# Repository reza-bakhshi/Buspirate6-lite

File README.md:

# ⚠️ THIS PROJECT IS UNDER ACTIVE DEVELOPMENT AND TESTING  

## DO NOT MANUFACTURE OR USE THE HARDWARE WITHOUT YOUR OWN VERIFICATION

## Overview

This project is currently in progress. Features, hardware design, and functionality may change at any time. Use at your own risk.

---

## Images

### TOP

### BOTTOM

---

## Notes

- This project is not stable yet.
- Hardware and firmware are still being tested.
- Double-check everything before using or manufacturing.

---

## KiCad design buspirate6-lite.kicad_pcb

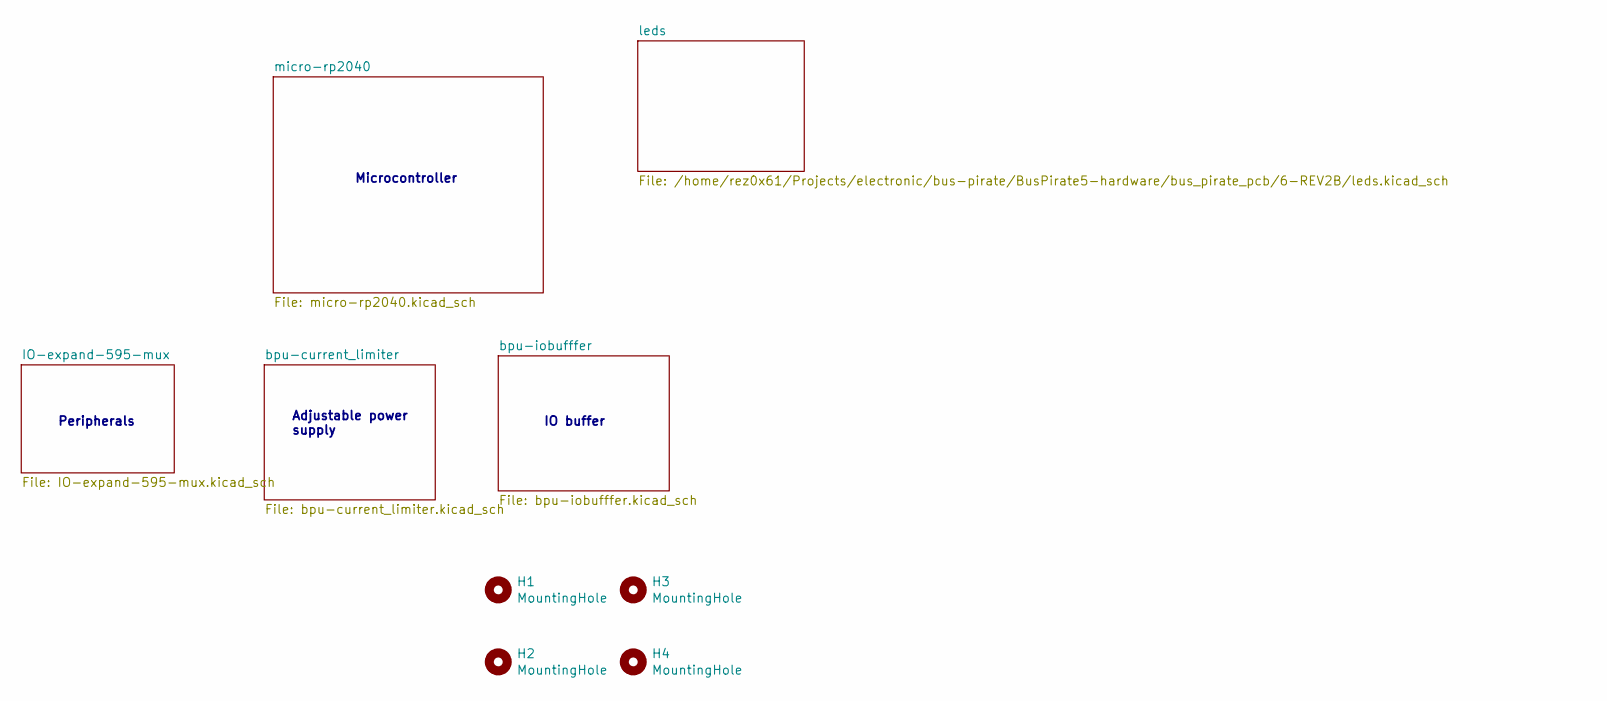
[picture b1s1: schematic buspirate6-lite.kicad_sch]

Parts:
H1, H2, H3, H4: MountingHole; MountingHole_2.2mm_M2

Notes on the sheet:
Microcontroller
Adjustable power supply
IO buffer
Peripherals

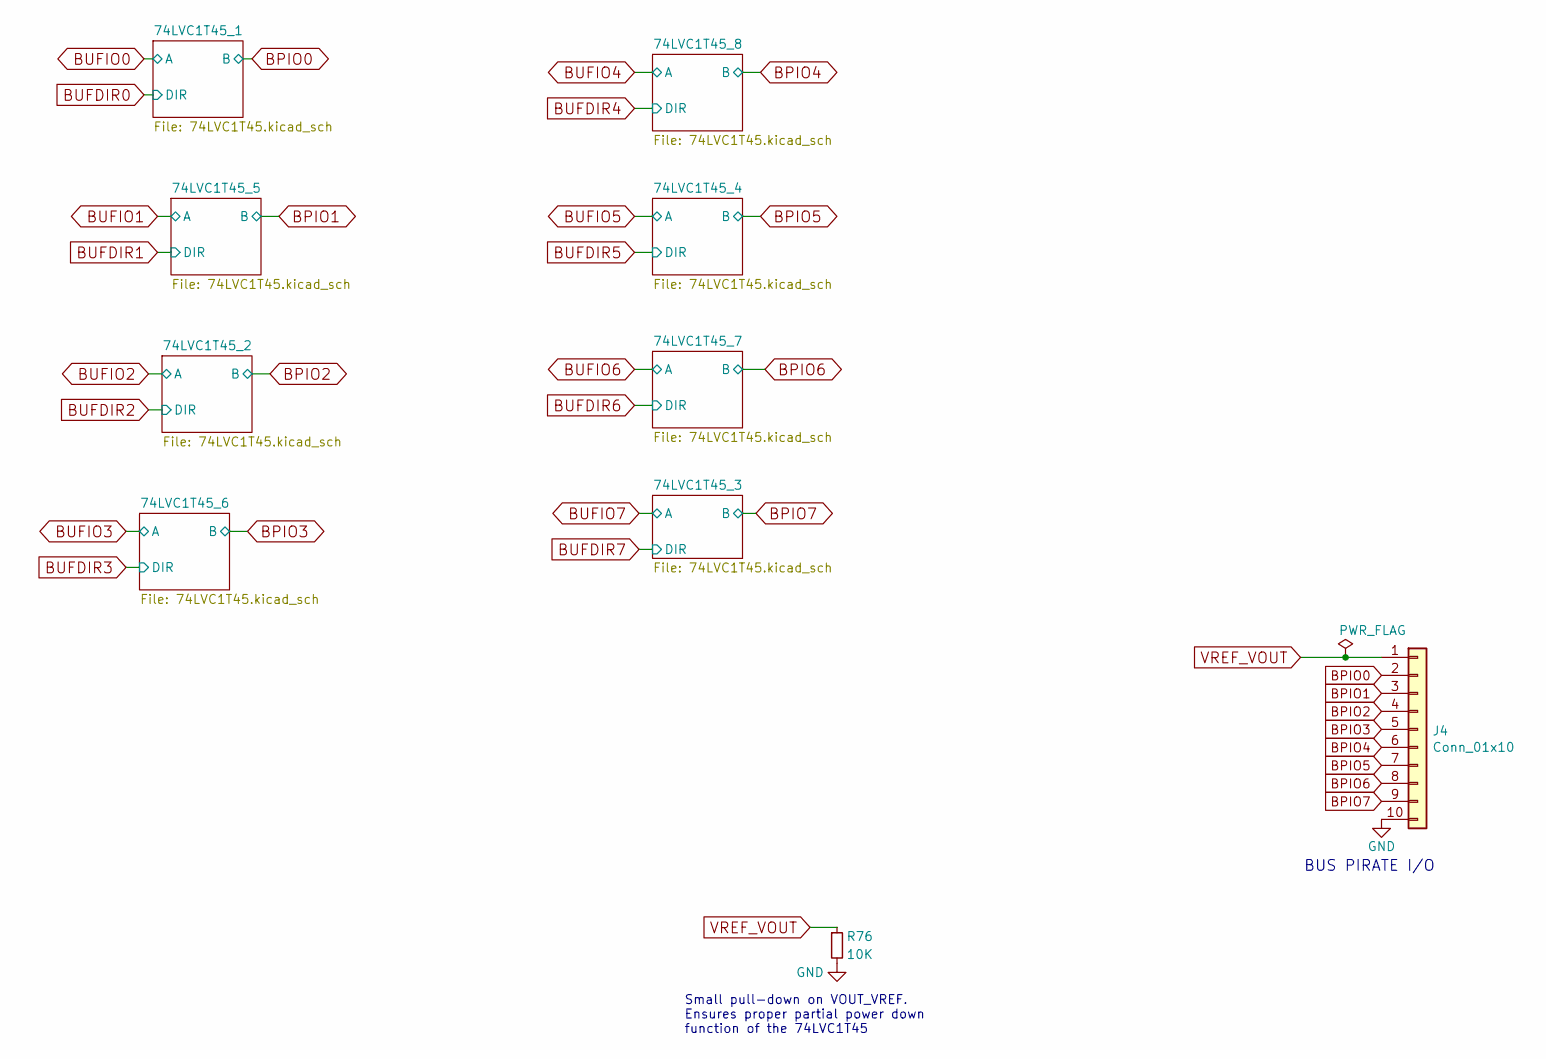
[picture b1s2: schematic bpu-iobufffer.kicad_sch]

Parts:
J4: Conn_01x10; PinHeader_1x10_P2.54mm_Vertical
R76: 10K; R_0402_1005Metric

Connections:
BPIO0: J4.2; also elsewhere on the board
BPIO1: J4.3; also elsewhere on the board
BPIO2: J4.4; also elsewhere on the board
BPIO3: J4.5; also elsewhere on the board
BPIO4: J4.6; also elsewhere on the board
BPIO5: J4.7; also elsewhere on the board
BPIO6: J4.8; also elsewhere on the board
BPIO7: J4.9; also elsewhere on the board
GND: J4.10, R76.2; also elsewhere on the board
VREF_VOUT: J4.1, R76.1; also elsewhere on the board

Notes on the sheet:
Small pull-down on VOUT_VREF. Ensures proper partial power down function of the 74LVC1T45
BUS PIRATE I/O

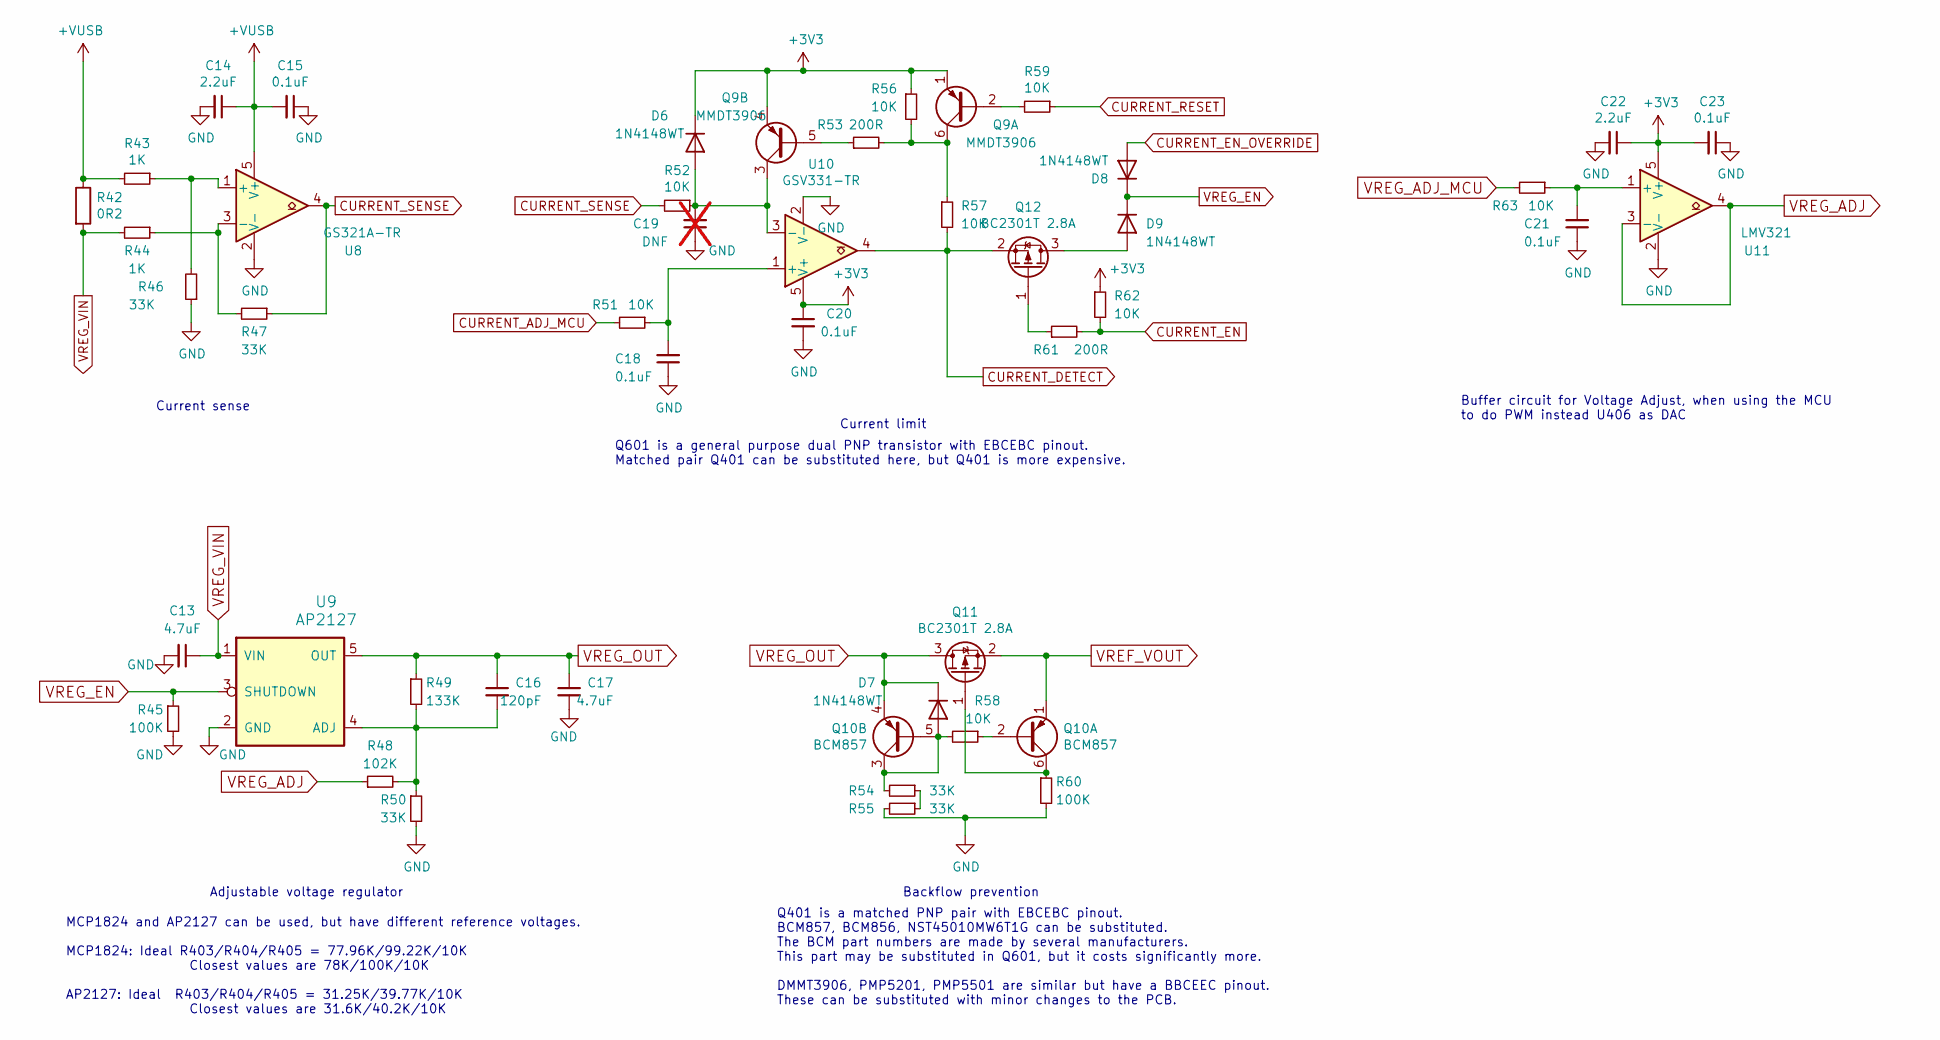
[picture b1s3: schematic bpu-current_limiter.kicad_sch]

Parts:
C13, C17: 4.7uF; C_0402_1005Metric
C14, C22: 2.2uF; C_0402_1005Metric
C15, C18, C20, C21, C23: 0.1uF; C_0402_1005Metric
C16: 120pF; C_0402_1005Metric
C19: DNF; C_0402_1005Metric; not fitted
D6, D7, D8, D9: 1N4148WT; D_SOD-523
Q9: MMDT3906; SOT-363_SC-70-6
Q10: BCM857; SOT-363_SC-70-6
Q11, Q12: BC2301T 2.8A; SOT-523
R42: 0R2; R_2512_6332Metric_Pad1.40x3.35mm_HandSolder
R43, R44: 1K; R_0402_1005Metric
R45, R60: 100K; R_0402_1005Metric
R46, R47, R50, R54, R55: 33K; R_0402_1005Metric
R48: 102K; R_0402_1005Metric
R49: 133K; R_0402_1005Metric
R51, R52, R56, R57, R58, R59, R62, R63: 10K; R_0402_1005Metric
R53, R61: 200R; R_0402_1005Metric
U8: GS321A-TR; SOT-23-5
U9: AP2127; SOT-23-5
U10: GSV331-TR; SOT-23-5
U11: LMV321; SOT-23-5

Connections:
+3V3: C20.1, C22.1, C23.2, D6.1 (K), Q9.1 (E1), Q9.4 (E2), R56.1, R62.1, U10.5 (V+), U11.5 (V+); also elsewhere on the board
+VUSB: C14.1, C15.2, R42.1, R43.2, U8.5 (V+); also elsewhere on the board
CURRENT_ADJ_MCU: R51.2; also elsewhere on the board
CURRENT_DETECT: Q12.2 (S), R57.2, U10.4; also elsewhere on the board
CURRENT_EN: R61.2, R62.2; also elsewhere on the board
CURRENT_EN_OVERRIDE: D8.2 (A); also elsewhere on the board
CURRENT_RESET: R59.1; also elsewhere on the board
CURRENT_SENSE: R47.1, R52.2, U8.4; also elsewhere on the board
GND: C13.2, C14.2, C15.1, C17.2, C18.1, C19.1, C20.2, C21.1, C22.2, C23.1, R45.2, R46.1, R50.2, R55.2, R60.2, U8.2 (V-), U9.2 (GND), U10.2 (V-), U11.2 (V-); also elsewhere on the board
unnamed: C19.2, D6.2 (A), Q9.3 (C2), R52.1, U10.3 (-)
unnamed: D7.2 (A), Q10.3 (C2), Q10.5 (B2), R54.2, R58.2
unnamed: D9.2 (A), Q12.3 (D)
unnamed: Q9.2 (B1), R59.2
unnamed: Q9.6 (C1), R53.2, R56.2, R57.1
unnamed: Q9.5 (B2), R53.1
unnamed: Q10.2 (B1), R58.1
unnamed: Q10.6 (C1), Q11.1 (G), R60.1
unnamed: Q12.1 (G), R61.1
unnamed: R54.1, R55.1
unnamed: R43.1, R46.2, U8.1 (+)
unnamed: R44.1, R47.2, U8.3 (-)
unnamed: C16.2, R48.2, R49.2, R50.1, U9.4 (ADJ)
unnamed: C18.2, R51.1, U10.1 (+)
unnamed: C21.2, R63.1, U11.1 (+)
VREF_VOUT: Q10.1 (E1), Q11.2 (S); also elsewhere on the board
VREG_ADJ: R48.1, U11.3 (-), U11.4
VREG_ADJ_MCU: R63.2; also elsewhere on the board
VREG_EN: D8.1 (K), D9.1 (K), R45.1, U9.3 (SHUTDOWN)
VREG_OUT: C16.1, C17.1, D7.1 (K), Q10.4 (E2), Q11.3 (D), R49.1, U9.5 (OUT); also elsewhere on the board
VREG_VIN: C13.1, R42.2, R44.2, U9.1 (VIN)

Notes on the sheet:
Adjustable voltage regulator
Buffer circuit for Voltage Adjust, when using the MCU to do PWM instead U406 as DAC
Current sense
Backflow prevention
MCP1824 and AP2127 can be used, but have different reference voltages. MCP1824: Ideal R403/R404/R405 = 77.96K/99.22K/10K Closest values are 78K/100K/10K AP2127: Ideal R403/R404/R405 = 31.25K/39.77K/10K Closest values are 31.6K/40.2K/10K
Current limit
Q401 is a matched PNP pair with EBCEBC pinout. BCM857, BCM856, NST45010MW6T1G can be substituted. The BCM part numbers are made by several manufacturers. This part may be substituted in Q601, but it costs significantly more. DMMT3906, PMP5201, PMP5501 are similar but have a BBCEEC pinout. These can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
Q601 is a general purpose dual PNP transistor with EBCEBC pinout. Matched pair Q401 can be substituted here, but Q401 is more expensive.

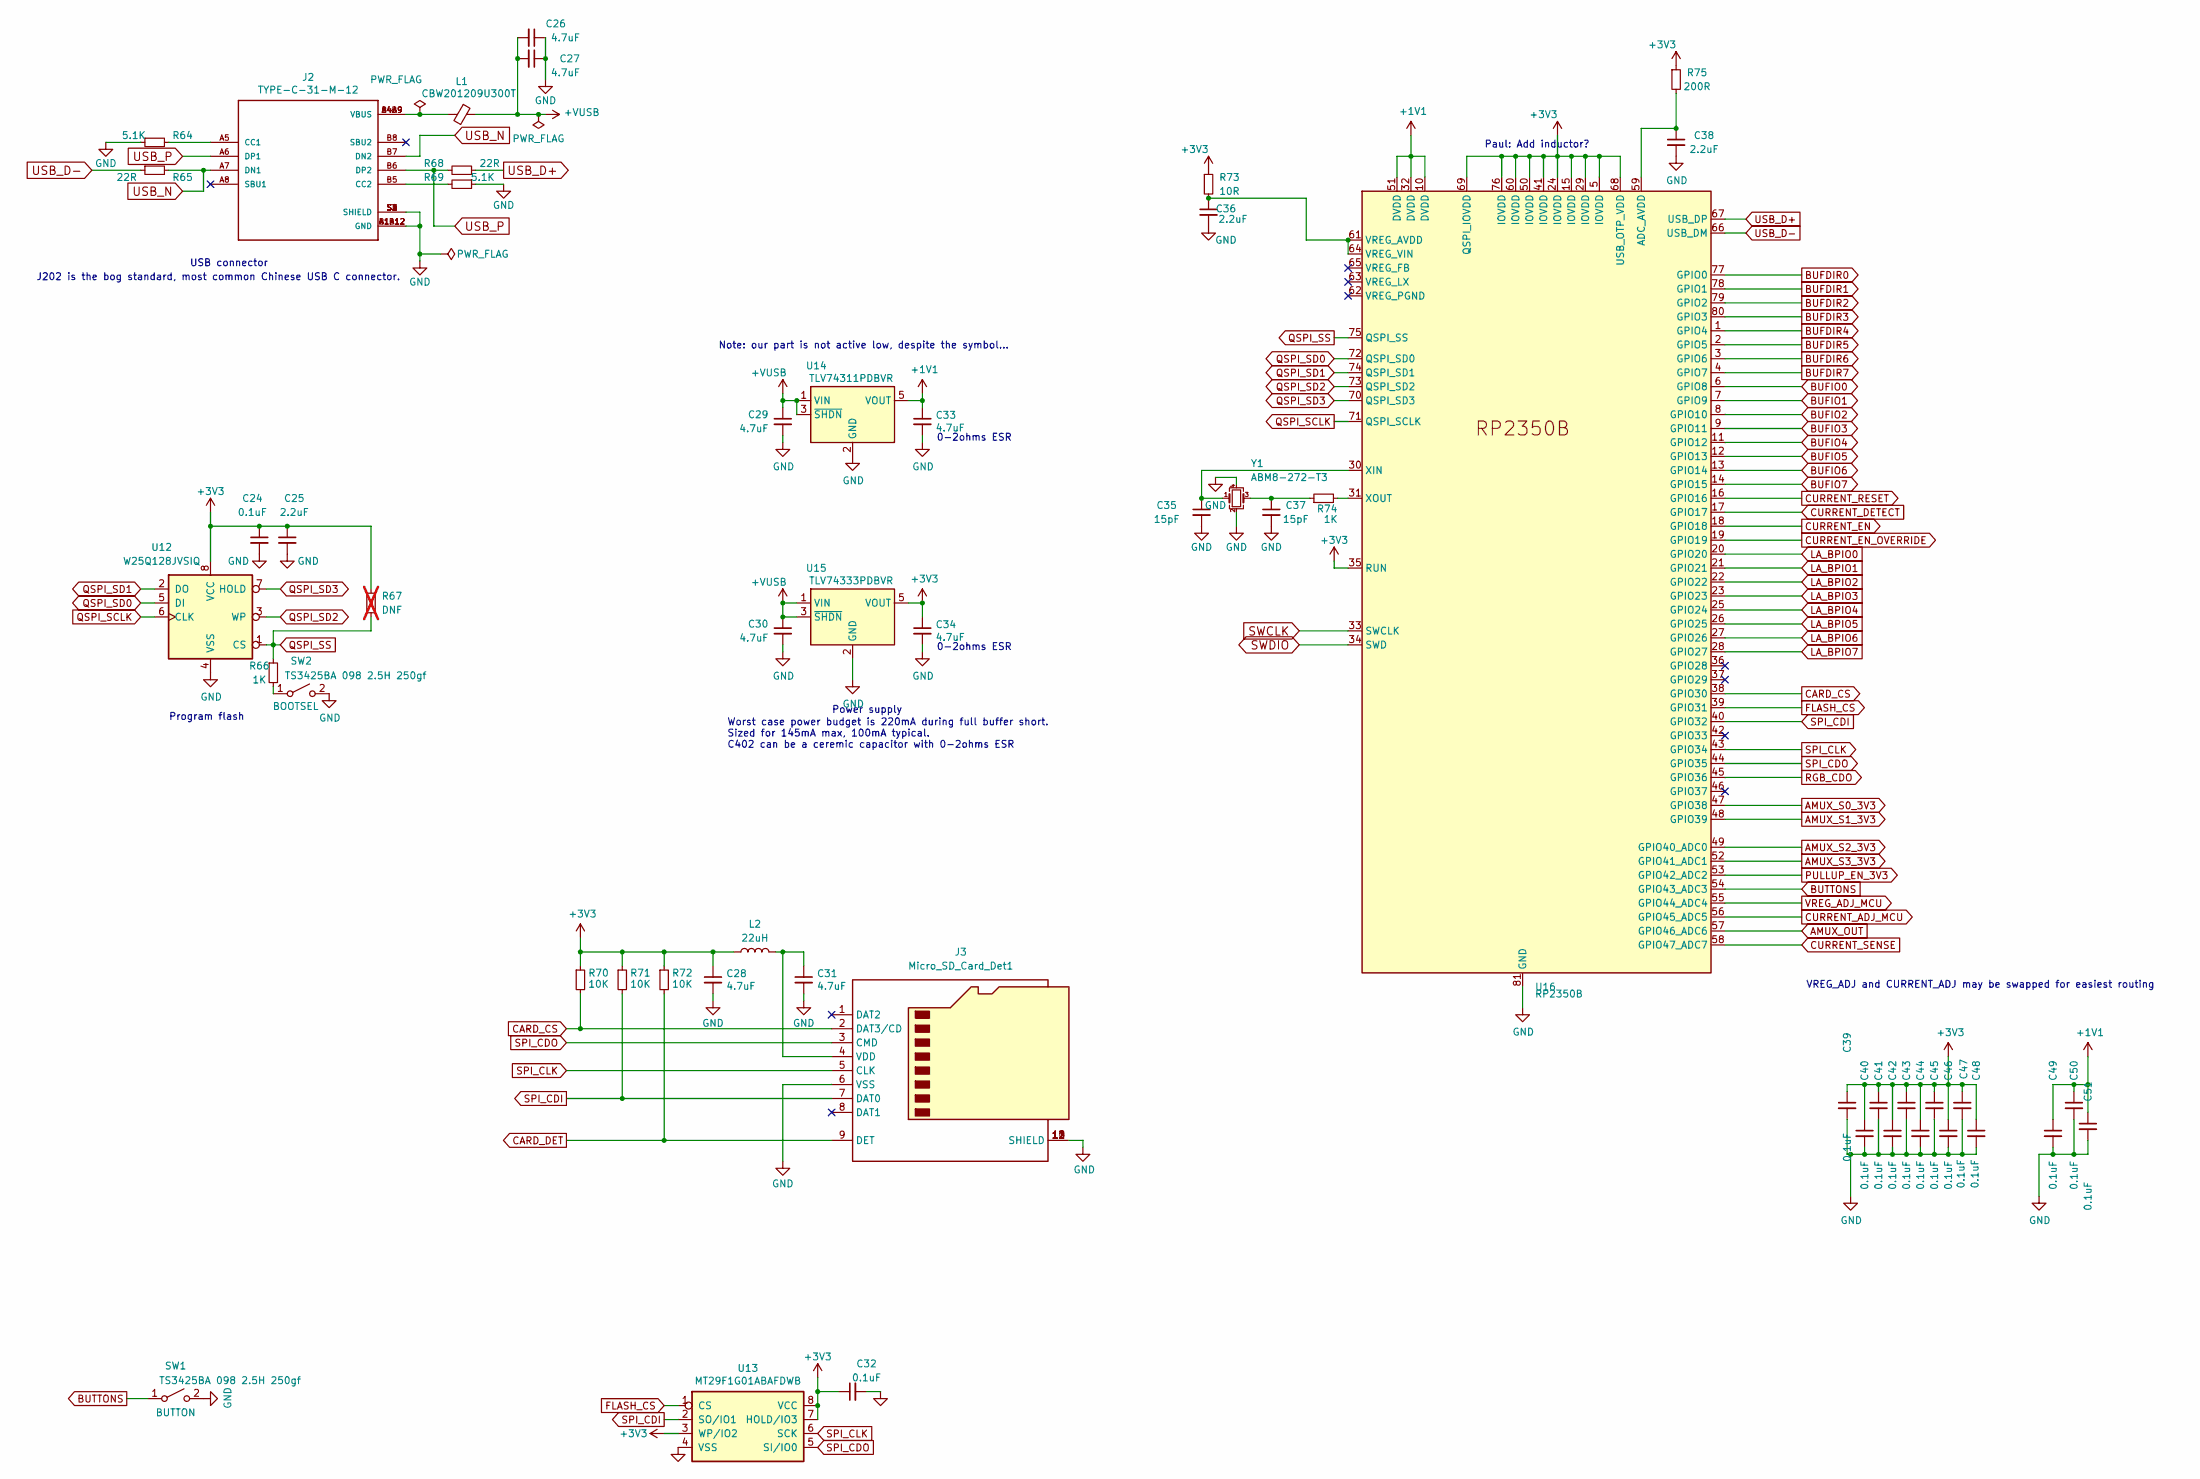
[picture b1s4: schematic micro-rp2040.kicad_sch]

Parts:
C24, C32, C39, C40, C41, C42, C43, C44, C45, C46, C47, C48, C49, C50, C51: 0.1uF; C_0402_1005Metric
C25, C36, C38: 2.2uF; C_0402_1005Metric
C26, C27, C28, C29, C30, C31, C33, C34: 4.7uF; C_0402_1005Metric
C35, C37: 15pF; C_0402_1005Metric
J2: TYPE-C-31-M-12; HRO_TYPE-C-31-M-12
J3: Micro_SD_Card_Det1; microSD_External_Pin
L1: CBW201209U300T; L_0805_2012Metric
L2: 22uH; L_0402_1005Metric
R64, R69: 5.1K; R_0402_1005Metric
R65, R68: 22R; R_0402_1005Metric
R66, R74: 1K; R_0402_1005Metric
R67: DNF; R_0402_1005Metric; not fitted
R70, R71, R72: 10K; R_0402_1005Metric
R73: 10R; R_0402_1005Metric
R75: 200R; R_0402_1005Metric
SW1, SW2: TS3425BA 098 2.5H 250gf; SW_SPST_PTS810
U12: W25Q128JVSIQ; SOP-8_5.28x5.23mm_P1.27mm
U13: MT29F1G01ABAFDWB; U-PDFN-8
U14: TLV74311PDBVR; SOT-23-5
U15: TLV74333PDBVR; SOT-23-5
U16: RP2350B; qfn80
Y1: ABM8-272-T3; Crystal_SMD_4Pin

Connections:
+1V1: C33.1, C49.1, C50.1, C51.1, U14.5 (VOUT), U16.10 (DVDD), U16.32 (DVDD), U16.51 (DVDD)
+3V3: C24.1, C25.1, C28.1, C32.1, C34.1, C39.1, C40.1, C41.1, C42.1, C43.1, C44.1, C45.1, C46.1, C47.1, C48.1, L2.1, R67.1, R70.1, R71.1, R72.1, R73.1, R75.1, U12.8 (VCC), U13.3 (WP/IO2), U13.7 (HOLD/IO3), U13.8 (VCC), U15.5 (VOUT), U16.5 (IOVDD), U16.15 (IOVDD), U16.24 (IOVDD), U16.29 (IOVDD), U16.35 (RUN), U16.41 (IOVDD), U16.50 (IOVDD), U16.60 (IOVDD), U16.68 (USB_OTP_VDD), U16.69 (QSPI_IOVDD), U16.76 (IOVDD); also elsewhere on the board
+VUSB: C26.2, C27.2, C29.1, C30.1, L1.1, U14.1 (VIN), U14.3 (~SHDN), U15.1 (VIN), U15.3 (~SHDN); also elsewhere on the board
AMUX_OUT: U16.57 (GPIO46_ADC6); also elsewhere on the board
AMUX_S0_3V3: U16.47 (GPIO38); also elsewhere on the board
AMUX_S1_3V3: U16.48 (GPIO39); also elsewhere on the board
AMUX_S2_3V3: U16.49 (GPIO40_ADC0); also elsewhere on the board
AMUX_S3_3V3: U16.52 (GPIO41_ADC1); also elsewhere on the board
BUFDIR0: U16.77 (GPIO0); also elsewhere on the board
BUFDIR1: U16.78 (GPIO1); also elsewhere on the board
BUFDIR2: U16.79 (GPIO2); also elsewhere on the board
BUFDIR3: U16.80 (GPIO3); also elsewhere on the board
BUFDIR4: U16.1 (GPIO4); also elsewhere on the board
BUFDIR5: U16.2 (GPIO5); also elsewhere on the board
BUFDIR6: U16.3 (GPIO6); also elsewhere on the board
BUFDIR7: U16.4 (GPIO7); also elsewhere on the board
BUFIO0: U16.6 (GPIO8); also elsewhere on the board
BUFIO1: U16.7 (GPIO9); also elsewhere on the board
BUFIO2: U16.8 (GPIO10); also elsewhere on the board
BUFIO3: U16.9 (GPIO11); also elsewhere on the board
BUFIO4: U16.11 (GPIO12); also elsewhere on the board
BUFIO5: U16.12 (GPIO13); also elsewhere on the board
BUFIO6: U16.13 (GPIO14); also elsewhere on the board
BUFIO7: U16.14 (GPIO15); also elsewhere on the board
BUTTONS: SW1.1 (A), U16.54 (GPIO43_ADC3)
CARD_CS: J3.2 (DAT3/CD), R70.2, U16.38 (GPIO30)
CARD_DET: J3.9 (DET), R72.2; also elsewhere on the board
CURRENT_ADJ_MCU: U16.56 (GPIO45_ADC5); also elsewhere on the board
CURRENT_DETECT: U16.17 (GPIO17); also elsewhere on the board
CURRENT_EN: U16.18 (GPIO18); also elsewhere on the board
CURRENT_EN_OVERRIDE: U16.19 (GPIO19); also elsewhere on the board
CURRENT_RESET: U16.16 (GPIO16); also elsewhere on the board
CURRENT_SENSE: U16.58 (GPIO47_ADC7); also elsewhere on the board
FLASH_CS: U13.1 (CS), U16.39 (GPIO31)
GND: C24.2, C25.2, C26.1, C27.1, C28.2, C29.2, C30.2, C31.2, C32.2, C33.2, C34.2, C35.2, C36.2, C37.2, C38.2, C39.2, C40.2, C41.2, C42.2, C43.2, C44.2, C45.2, C46.2, C47.2, C48.2, C49.2, C50.2, C51.2, J2.A1B12 (GND), J2.B1A12 (GND), J2.S1 (SHIELD), J2.S2 (SHIELD), J2.S3 (SHIELD), J2.S4 (SHIELD), J3.6 (VSS), J3.10 (SHIELD), J3.11 (SHIELD), J3.12 (SHIELD), J3.13 (SHIELD), R64.1, R69.1, SW1.2 (B), SW2.2 (B), U12.4 (VSS), U13.4 (VSS), U14.2 (GND), U14.4 (GND), U15.2 (GND), U15.4 (GND), U16.81 (GND), Y1.2, Y1.4; also elsewhere on the board
LA_BPIO0: U16.20 (GPIO20); also elsewhere on the board
LA_BPIO1: U16.21 (GPIO21); also elsewhere on the board
LA_BPIO2: U16.22 (GPIO22); also elsewhere on the board
LA_BPIO3: U16.23 (GPIO23); also elsewhere on the board
LA_BPIO4: U16.25 (GPIO24); also elsewhere on the board
LA_BPIO5: U16.26 (GPIO25); also elsewhere on the board
LA_BPIO6: U16.27 (GPIO26); also elsewhere on the board
LA_BPIO7: U16.28 (GPIO27); also elsewhere on the board
unnamed: C37.1, R74.1, Y1.3
unnamed: J2.A5 (CC1), R64.2
unnamed: J2.B5 (CC2), R69.2
unnamed: J2.A4B9 (VBUS), J2.B4A9 (VBUS), L1.2
unnamed: C31.1, J3.4 (VDD), L2.2
unnamed: R66.2, SW2.1 (A)
unnamed: C38.1, R75.2, U16.59 (ADC_AVDD)
unnamed: C36.1, R73.2, U16.61 (VREG_AVDD), U16.64 (VREG_VIN)
unnamed: C35.1, U16.30 (XIN), Y1.1
unnamed: R74.2, U16.31 (XOUT)
PULLUP_EN_3V3: U16.53 (GPIO42_ADC2); also elsewhere on the board
QSPI_SCLK: U12.6 (CLK), U16.71 (QSPI_SCLK)
QSPI_SD0: U12.5 (DI), U16.72 (QSPI_SD0)
QSPI_SD1: U12.2 (DO), U16.74 (QSPI_SD1)
QSPI_SD2: U12.3 (WP), U16.73 (QSPI_SD2)
QSPI_SD3: U12.7 (HOLD), U16.70 (QSPI_SD3)
QSPI_SS: R66.1, R67.2, U12.1 (CS), U16.75 (QSPI_SS)
RGB_CDO: U16.45 (GPIO36); also elsewhere on the board
SPI_CDI: J3.7 (DAT0), R71.2, U13.2 (SO/IO1), U16.40 (GPIO32)
SPI_CDO: J3.3 (CMD), U13.5 (SI/IO0), U16.44 (GPIO35)
SPI_CLK: J3.5 (CLK), U13.6 (SCK), U16.43 (GPIO34)
SWCLK: U16.33 (SWCLK)
SWDIO: U16.34 (SWD)
USB_D+: R68.1, U16.67 (USB_DP)
USB_D-: R65.1, U16.66 (USB_DM)
USB_N: J2.A7 (DN1), J2.B7 (DN2), R65.2
USB_P: J2.A6 (DP1), J2.B6 (DP2), R68.2
VREG_ADJ_MCU: U16.55 (GPIO44_ADC4); also elsewhere on the board

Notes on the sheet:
Note: our part is not active low, despite the symbol...
USB connector
Power supply
J202 is the bog standard, most common Chinese USB C connector.
Program flash
Worst case power budget is 220mA during full buffer short. Sized for 145mA max, 100mA typical. C402 can be a ceremic capacitor with 0-2ohms ESR
Paul: Add inductor?
VREG_ADJ and CURRENT_ADJ may be swapped for easiest routing
0-2ohms ESR

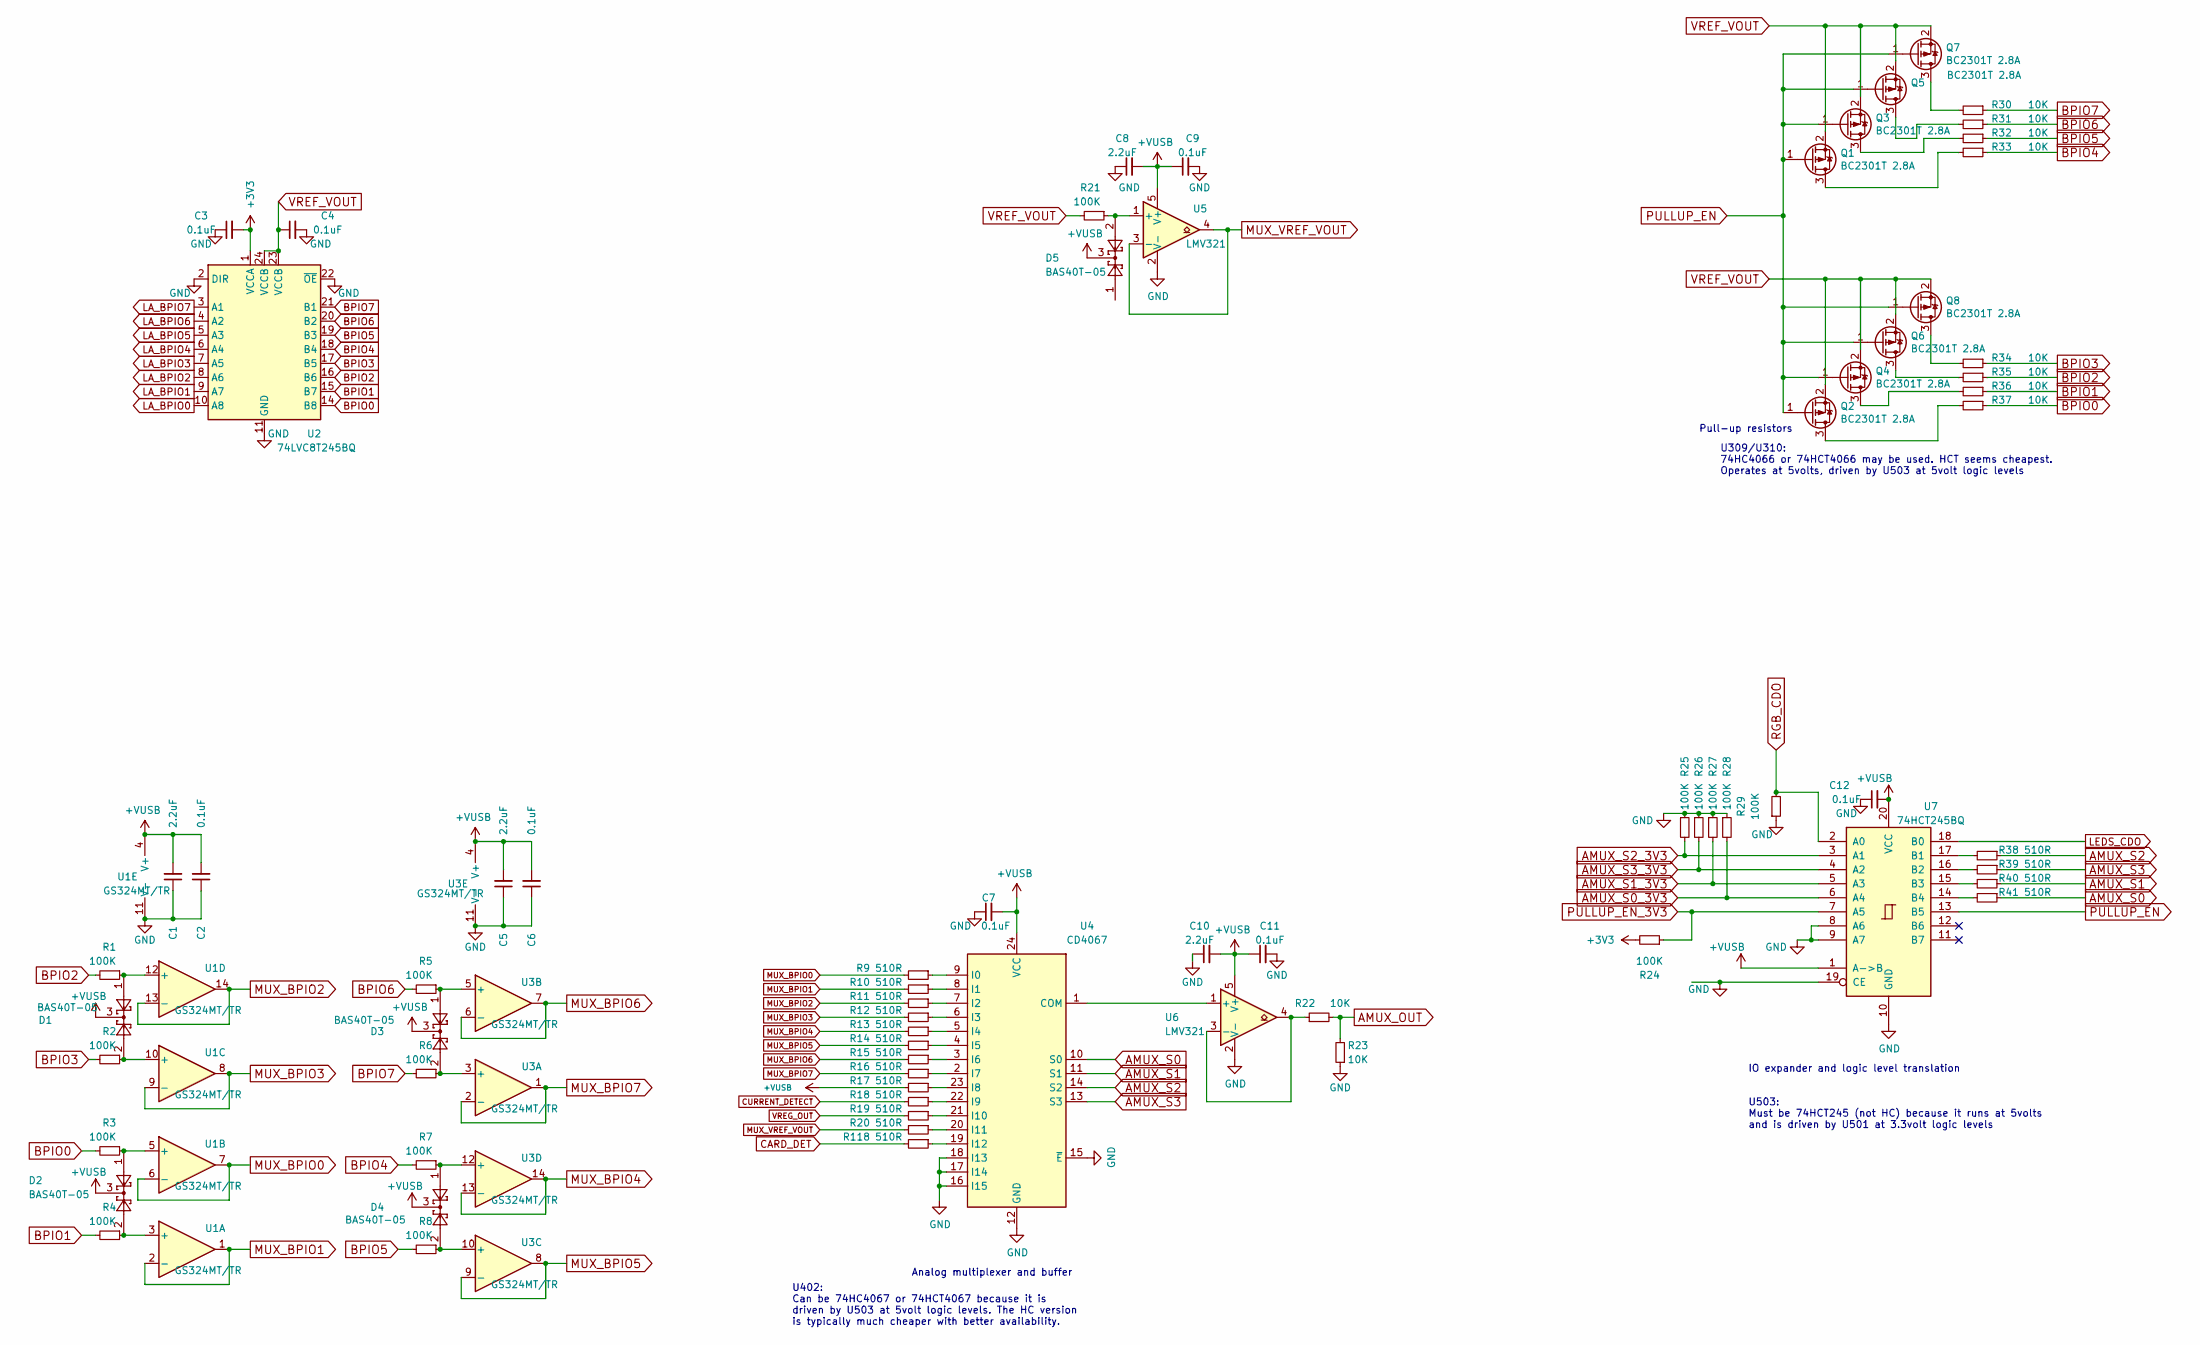
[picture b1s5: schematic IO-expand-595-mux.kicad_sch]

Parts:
C1, C5, C8, C10: 2.2uF; C_0402_1005Metric
C2, C3, C4, C6, C7, C9, C11, C12: 0.1uF; C_0402_1005Metric
D1, D2, D3, D4, D5: BAS40T-05; SOT-523
Q1, Q2, Q3, Q4, Q5, Q6, Q7, Q8: BC2301T 2.8A; SOT-523
R1, R2, R3, R4, R5, R6, R7, R8, R21, R24, R25, R26, R27, R28, R29: 100K; R_0402_1005Metric
R9, R10, R11, R12, R13, R14, R15, R16, R17, R18, R19, R20, R38, R39, R40, R41, R118: 510R; R_0402_1005Metric
R22, R23, R30, R31, R32, R33, R34, R35, R36, R37: 10K; R_0402_1005Metric
U1, U3: GS324MT/TR; TSSOP-14_4.4x5mm_P0.65mm
U2: 74LVC8T245BQ; TSSOP-24_4.4x7.8mm_P0.65mm
U4: CD4067; TSSOP-24_4.4x7.8mm_P0.65mm
U5, U6: LMV321; SOT-23-5
U7: 74HCT245BQ; TSSOP-20_4.4x6.5mm_P0.65mm

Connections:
+3V3: C3.2, R24.2, U2.1 (VCCA); also elsewhere on the board
+VUSB: C1.2, C2.2, C5.2, C6.2, C7.2, C8.2, C9.1, C10.2, C11.1, C12.2, D1.3, D2.3, D3.3, D4.3, D5.3, R17.2, U1.4 (V+), U3.4 (V+), U4.24 (VCC), U5.5 (V+), U6.5 (V+), U7.1 (A->B), U7.20 (VCC); also elsewhere on the board
AMUX_OUT: R22.2, R23.2; also elsewhere on the board
AMUX_S0: R41.1, U4.10 (S0)
AMUX_S0_3V3: R28.2, U7.6 (A4); also elsewhere on the board
AMUX_S1: R40.1, U4.11 (S1)
AMUX_S1_3V3: R27.2, U7.5 (A3); also elsewhere on the board
AMUX_S2: R38.1, U4.14 (S2)
AMUX_S2_3V3: R25.2, U7.3 (A1); also elsewhere on the board
AMUX_S3: R39.1, U4.13 (S3)
AMUX_S3_3V3: R26.2, U7.4 (A2); also elsewhere on the board
BPIO0: R3.2, R37.1, U2.14 (B8); also elsewhere on the board
BPIO1: R4.2, R36.1, U2.15 (B7); also elsewhere on the board
BPIO2: R1.2, R35.1, U2.16 (B6); also elsewhere on the board
BPIO3: R2.2, R34.1, U2.17 (B5); also elsewhere on the board
BPIO4: R7.2, R33.1, U2.18 (B4); also elsewhere on the board
BPIO5: R8.2, R32.1, U2.19 (B3); also elsewhere on the board
BPIO6: R5.2, R31.1, U2.20 (B2); also elsewhere on the board
BPIO7: R6.2, R30.1, U2.21 (B1); also elsewhere on the board
CARD_DET: R118.2; also elsewhere on the board
CURRENT_DETECT: R18.2; also elsewhere on the board
GND: C1.1, C2.1, C3.1, C4.2, C5.1, C6.1, C7.1, C8.1, C9.2, C10.1, C11.2, C12.1, R23.1, R25.1, R26.1, R27.1, R28.1, R29.1, U1.11 (V-), U2.2 (DIR), U2.11 (GND), U2.12 (GND), U2.13 (GND), U2.22 (~OE), U3.11 (V-), U4.12 (GND), U4.15 (~E), U4.16 (I15), U4.17 (I14), U4.18 (I13), U5.2 (V-), U6.2 (V-), U7.8 (A6), U7.9 (A7), U7.10 (GND), U7.19 (CE); also elsewhere on the board
LA_BPIO0: U2.10 (A8); also elsewhere on the board
LA_BPIO1: U2.9 (A7); also elsewhere on the board
LA_BPIO2: U2.8 (A6); also elsewhere on the board
LA_BPIO3: U2.7 (A5); also elsewhere on the board
LA_BPIO4: U2.6 (A4); also elsewhere on the board
LA_BPIO5: U2.5 (A3); also elsewhere on the board
LA_BPIO6: U2.4 (A2); also elsewhere on the board
LA_BPIO7: U2.3 (A1); also elsewhere on the board
LEDS_CDO: U7.18 (B0); also elsewhere on the board
MUX_BPIO0: R9.2, U1.6 (-), U1.7
MUX_BPIO1: R10.2, U1.1, U1.2 (-)
MUX_BPIO2: R11.2, U1.13 (-), U1.14
MUX_BPIO3: R12.2, U1.8, U1.9 (-)
MUX_BPIO4: R13.2, U3.13 (-), U3.14
MUX_BPIO5: R14.2, U3.8, U3.9 (-)
MUX_BPIO6: R15.2, U3.6 (-), U3.7
MUX_BPIO7: R16.2, U3.1, U3.2 (-)
MUX_VREF_VOUT: R20.2, U5.3 (-), U5.4
unnamed: Q1.3 (D), R33.2
unnamed: Q2.3 (D), R37.2
unnamed: Q3.3 (D), R32.2
unnamed: Q4.3 (D), R36.2
unnamed: Q5.3 (D), R31.2
unnamed: Q6.3 (D), R35.2
unnamed: Q7.3 (D), R30.2
unnamed: Q8.3 (D), R34.2
unnamed: D2.2, R4.1, U1.3 (+)
unnamed: D2.1, R3.1, U1.5 (+)
unnamed: D1.2, R2.1, U1.10 (+)
unnamed: D1.1, R1.1, U1.12 (+)
unnamed: D3.2, R6.1, U3.3 (+)
unnamed: D3.1, R5.1, U3.5 (+)
unnamed: D4.2, R8.1, U3.10 (+)
unnamed: D4.1, R7.1, U3.12 (+)
unnamed: U4.1 (COM), U6.1 (+)
unnamed: R9.1, U4.9 (I0)
unnamed: R10.1, U4.8 (I1)
unnamed: R11.1, U4.7 (I2)
unnamed: R12.1, U4.6 (I3)
unnamed: R13.1, U4.5 (I4)
unnamed: R14.1, U4.4 (I5)
unnamed: R15.1, U4.3 (I6)
unnamed: R16.1, U4.2 (I7)
unnamed: R17.1, U4.23 (I8)
unnamed: R18.1, U4.22 (I9)
unnamed: R19.1, U4.21 (I10)
unnamed: R20.1, U4.20 (I11)
unnamed: R118.1, U4.19 (I12)
unnamed: D5.2, R21.1, U5.1 (+)
unnamed: R22.1, U6.3 (-), U6.4
unnamed: R38.2, U7.17 (B1)
unnamed: R39.2, U7.16 (B2)
unnamed: R40.2, U7.15 (B3)
unnamed: R41.2, U7.14 (B4)
PULLUP_EN: Q1.1 (G), Q2.1 (G), Q3.1 (G), Q4.1 (G), Q5.1 (G), Q6.1 (G), Q7.1 (G), Q8.1 (G), U7.13 (B5)
PULLUP_EN_3V3: R24.1, U7.7 (A5); also elsewhere on the board
RGB_CDO: R29.2, U7.2 (A0); also elsewhere on the board
VREF_VOUT: C4.1, Q1.2 (S), Q2.2 (S), Q3.2 (S), Q4.2 (S), Q5.2 (S), Q6.2 (S), Q7.2 (S), Q8.2 (S), R21.2, U2.23 (VCCB), U2.24 (VCCB); also elsewhere on the board
VREG_OUT: R19.2; also elsewhere on the board

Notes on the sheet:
IO expander and logic level translation
Analog multiplexer and buffer
U402: Can be 74HC4067 or 74HCT4067 because it is driven by U503 at 5volt logic levels. The HC version is typically much cheaper with better availability.
U503: Must be 74HCT245 (not HC) because it runs at 5volts and is driven by U501 at 3.3volt logic levels
U309/U310: 74HC4066 or 74HCT4066 may be used. HCT seems cheapest. Operates at 5volts, driven by U503 at 5volt logic levels
Pull-up resistors

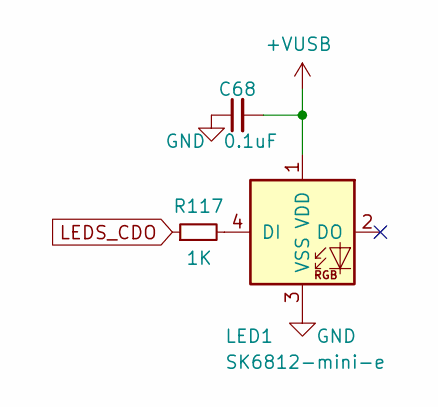
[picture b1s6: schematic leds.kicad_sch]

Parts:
C68: 0.1uF; C_0402_1005Metric
LED1: SK6812-mini-e
R117: 1K; R_0402_1005Metric

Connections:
+VUSB: C68.2, LED1.1 (VDD); also elsewhere on the board
GND: C68.1, LED1.3 (VSS); also elsewhere on the board
LEDS_CDO: R117.1; also elsewhere on the board
unnamed: LED1.4 (DI), R117.2

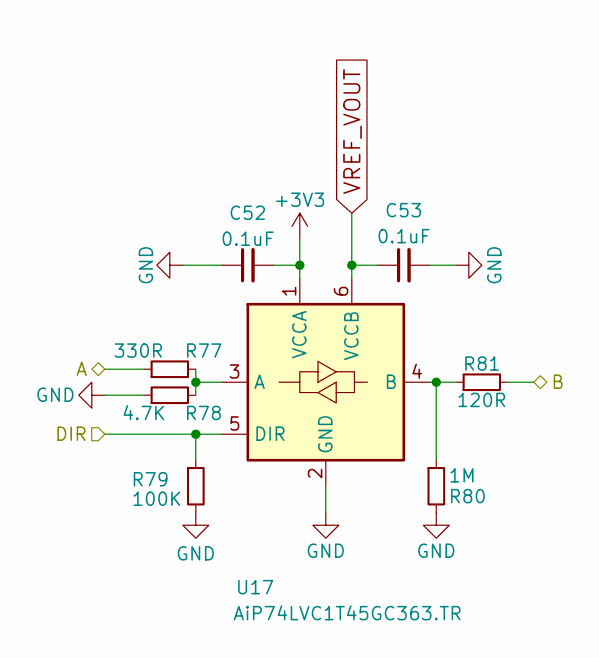
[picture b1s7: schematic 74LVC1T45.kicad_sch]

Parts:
C52, C53: 0.1uF; C_0402_1005Metric
R77: 330R; R_0402_1005Metric
R78: 4.7K; R_0402_1005Metric
R79: 100K; R_0402_1005Metric
R80: 1M; R_0402_1005Metric
R81: 120R; R_0402_1005Metric
U17: AiP74LVC1T45GC363.TR; SOT-363_SC-70-6

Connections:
+3V3: C52.2, U17.1 (VCCA); also elsewhere on the board
BPIO0: R81.2; also elsewhere on the board
BUFDIR0: R79.1, U17.5 (DIR); also elsewhere on the board
BUFIO0: R77.1; also elsewhere on the board
GND: C52.1, C53.2, R78.1, R79.2, R80.2, U17.2 (GND); also elsewhere on the board
unnamed: R77.2, R78.2, U17.3 (A)
unnamed: R80.1, R81.1, U17.4 (B)
VREF_VOUT: C53.1, U17.6 (VCCB); also elsewhere on the board

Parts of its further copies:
C54, C55, C56, C57, C58, C59, C60, C61, C62, C63, C64, C65, C66, C67: 0.1uF; C_0402_1005Metric
R82, R87, R92, R97, R102, R107, R112: 330R; R_0402_1005Metric
R83, R88, R93, R98, R103, R108, R113: 4.7K; R_0402_1005Metric
R84, R89, R94, R99, R104, R109, R114: 100K; R_0402_1005Metric
R85, R90, R95, R100, R105, R110, R115: 1M; R_0402_1005Metric
R86, R91, R96, R101, R106, R111, R116: 120R; R_0402_1005Metric
U18, U19, U20, U21, U22, U23, U24: AiP74LVC1T45GC363.TR; SOT-363_SC-70-6

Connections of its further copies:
+3V3: C54.2, C56.2, C58.2, C60.2, C62.2, C64.2, C66.2, U18.1 (VCCA), U19.1 (VCCA), U20.1 (VCCA), U21.1 (VCCA), U22.1 (VCCA), U23.1 (VCCA), U24.1 (VCCA); also elsewhere on the board
BPIO1: R101.2; also elsewhere on the board
BPIO2: R86.2; also elsewhere on the board
BPIO3: R106.2; also elsewhere on the board
BPIO4: R116.2; also elsewhere on the board
BPIO5: R96.2; also elsewhere on the board
BPIO6: R111.2; also elsewhere on the board
BPIO7: R91.2; also elsewhere on the board
BUFDIR1: R99.1, U21.5 (DIR); also elsewhere on the board
BUFDIR2: R84.1, U18.5 (DIR); also elsewhere on the board
BUFDIR3: R104.1, U22.5 (DIR); also elsewhere on the board
BUFDIR4: R114.1, U24.5 (DIR); also elsewhere on the board
BUFDIR5: R94.1, U20.5 (DIR); also elsewhere on the board
BUFDIR6: R109.1, U23.5 (DIR); also elsewhere on the board
BUFDIR7: R89.1, U19.5 (DIR); also elsewhere on the board
BUFIO1: R97.1; also elsewhere on the board
BUFIO2: R82.1; also elsewhere on the board
BUFIO3: R102.1; also elsewhere on the board
BUFIO4: R112.1; also elsewhere on the board
BUFIO5: R92.1; also elsewhere on the board
BUFIO6: R107.1; also elsewhere on the board
BUFIO7: R87.1; also elsewhere on the board
GND: C54.1, C55.2, C56.1, C57.2, C58.1, C59.2, C60.1, C61.2, C62.1, C63.2, C64.1, C65.2, C66.1, C67.2, R83.1, R84.2, R85.2, R88.1, R89.2, R90.2, R93.1, R94.2, R95.2, R98.1, R99.2, R100.2, R103.1, R104.2, R105.2, R108.1, R109.2, R110.2, R113.1, R114.2, R115.2, U18.2 (GND), U19.2 (GND), U20.2 (GND), U21.2 (GND), U22.2 (GND), U23.2 (GND), U24.2 (GND); also elsewhere on the board
unnamed: R82.2, R83.2, U18.3 (A)
unnamed: R85.1, R86.1, U18.4 (B)
unnamed: R87.2, R88.2, U19.3 (A)
unnamed: R90.1, R91.1, U19.4 (B)
unnamed: R92.2, R93.2, U20.3 (A)
unnamed: R95.1, R96.1, U20.4 (B)
unnamed: R97.2, R98.2, U21.3 (A)
unnamed: R100.1, R101.1, U21.4 (B)
unnamed: R102.2, R103.2, U22.3 (A)
unnamed: R105.1, R106.1, U22.4 (B)
unnamed: R107.2, R108.2, U23.3 (A)
unnamed: R110.1, R111.1, U23.4 (B)
unnamed: R112.2, R113.2, U24.3 (A)
unnamed: R115.1, R116.1, U24.4 (B)
VREF_VOUT: C55.1, C57.1, C59.1, C61.1, C63.1, C65.1, C67.1, U18.6 (VCCB), U19.6 (VCCB), U20.6 (VCCB), U21.6 (VCCB), U22.6 (VCCB), U23.6 (VCCB), U24.6 (VCCB); also elsewhere on the board
